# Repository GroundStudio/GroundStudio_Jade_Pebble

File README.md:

GroundStudio Jade Pebble
====================================

Get it from [ardushop.ro](https://ardushop.ro/en/development-boards/1052-placa-de-dezvoltare-jade-pebble-6427854000668.html)

Explore all the GroundStudio products at [ardushop.ro](https://ardushop.ro/en/37-groundstudio)

Description
-------------------
Very small SAMD21E18A based development board wih 48 MHz 32 bit processor, 256kBytes of Programmable Flash program memory, 32kBytes Internal SRAM, 6 Capacitive Touch sensing (PTC), 9 PWM Channels, 11 Digital Pins, 9 channel 12 bit ADC Pins and built in RGB NeoPixel LED.

Contents
-------------------

* [/Documentation](https://github.com/GroundStudio/GroundStudio_Jade_Pebble/tree/main/Documentation) -- Pinout.
* [/Hardware](https://github.com/GroundStudio/GroundStudio_Jade_Pebble/tree/main/Hardware) -- Schematics, layout.

Versions
-------------------
*(Not all tags shown)*

- [REV 0.1]

License
-------------------

This is released under the [Attribution-ShareAlike 4.0 International (CC BY-SA 4.0)](https://creativecommons.org/licenses/by-sa/4.0/) license.
**You are welcome to use this for commercial purposes.**

Please consider contributing back to this project or others to help the open-source hardware community continue to thrive and grow!

Certifications:

[Open Source Hardware Association](https://certification.oshwa.org/ro000005.html)   
   
[
](https://certification.oshwa.org/ro000005.html)

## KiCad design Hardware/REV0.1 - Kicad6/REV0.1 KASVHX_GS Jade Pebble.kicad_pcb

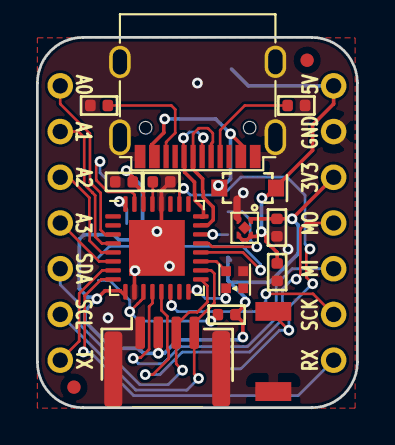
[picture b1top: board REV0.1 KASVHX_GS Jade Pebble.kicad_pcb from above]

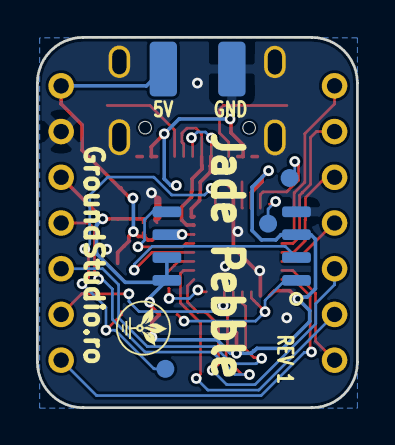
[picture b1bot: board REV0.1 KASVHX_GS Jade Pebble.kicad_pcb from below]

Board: 2 copper layers, 17.8 x 20.6 mm, 22 parts (3 on the bottom side), 29 nets.

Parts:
C1, C2, C3, C4: 1uF; C_0402_1005Metric
D1: D_Schottky; SOD-123
FID1, FID2: Fiducial; Fiducial_0.75mm_Mask1.5mm
J1, J2: Conn_01x07; PinHeader_1x07_P2.54mm_Slim_Vertical_Male
LED1: SK6805-EC15 DY-S1515065; SK6805-EC15
R1, R2, R3: 5.1k; R_0402_1005Metric
REG1: ME6211C33U4AG-N; FBP1-1-4
SW1: TS342A2P-WZ
TP1: TP_!RESET; TestPoint
TP2: TP_SWCLK; TestPoint
TP3: TP_SWDIO; TestPoint
U1: ATSAMD21E18A-MUT; QFN-32-1EP_5x5mm_P0.5mm_EP3.1x3.1mm
U2: W25Q32JVSSIQ; SOIC-8_5.23x5.23mm_P1.27mm
USB1: USB_C_FULL; USB_C_C167321
X1: i2c_3V3; SH__1x04_P1.00mm_Horizontal

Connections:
!RESET: SW1.2, TP1.~, U1.26
+3V3: C2.1, C4.1, J1.5, R3.1, REG1.1, U1.9, U1.30, U2.3, U2.7, U2.8, X1.2
+5V: C1.1, D1.1, J1.7, REG1.3, REG1.4
A0: J2.1, U1.3
A1: J2.2, U1.4
A2: J2.3, U1.5
A3: J2.4, U1.6
D+: U1.24, USB1.A6, USB1.B6
D-: U1.23, USB1.A7, USB1.B7
FLASH_CS: R3.2, U1.11, U2.1
GND: C1.2, C2.2, C3.2, C4.2, J1.6, LED1.4, R1.2, R2.2, REG1.2, SW1.1, U1.10, U1.28, U1.33, U2.4, USB1.0, USB1.A1, USB1.A12, USB1.B1, USB1.B12, X1.0, X1.1
MISO: J1.3, U1.12
MISO2: U1.20, U2.2
MOSI: J1.4, U1.13
MOSI2: U1.21, U2.5
NEOPIX: LED1.1, U1.19
NEO_PWR: LED1.2, U1.16
unnamed: C3.1, U1.29
unnamed: R1.1, USB1.A5
unnamed: R2.1, USB1.B5
RX_A7: J1.1, U1.8
SCK: J1.2, U1.14
SCK2: U1.22, U2.6
SCL: J2.6, U1.18, X1.4
SDA: J2.5, U1.17, X1.3
SWCLK: TP2.~, U1.31
SWDIO: TP3.~, U1.32
TX_A6: J2.7, U1.7
VBUS: D1.2, USB1.A4, USB1.A9, USB1.B4, USB1.B9

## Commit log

2022-08-11 - initial commit
2022-08-26 - added schematic pdf file
2022-08-26 - added "Kicad6" to revision folder name
2023-03-15 Update README.md
    - removed references to "library"
2023-10-23 - fixed schematic title error
2023-11-03 - added datasheet
2025-09-10 update shop links
